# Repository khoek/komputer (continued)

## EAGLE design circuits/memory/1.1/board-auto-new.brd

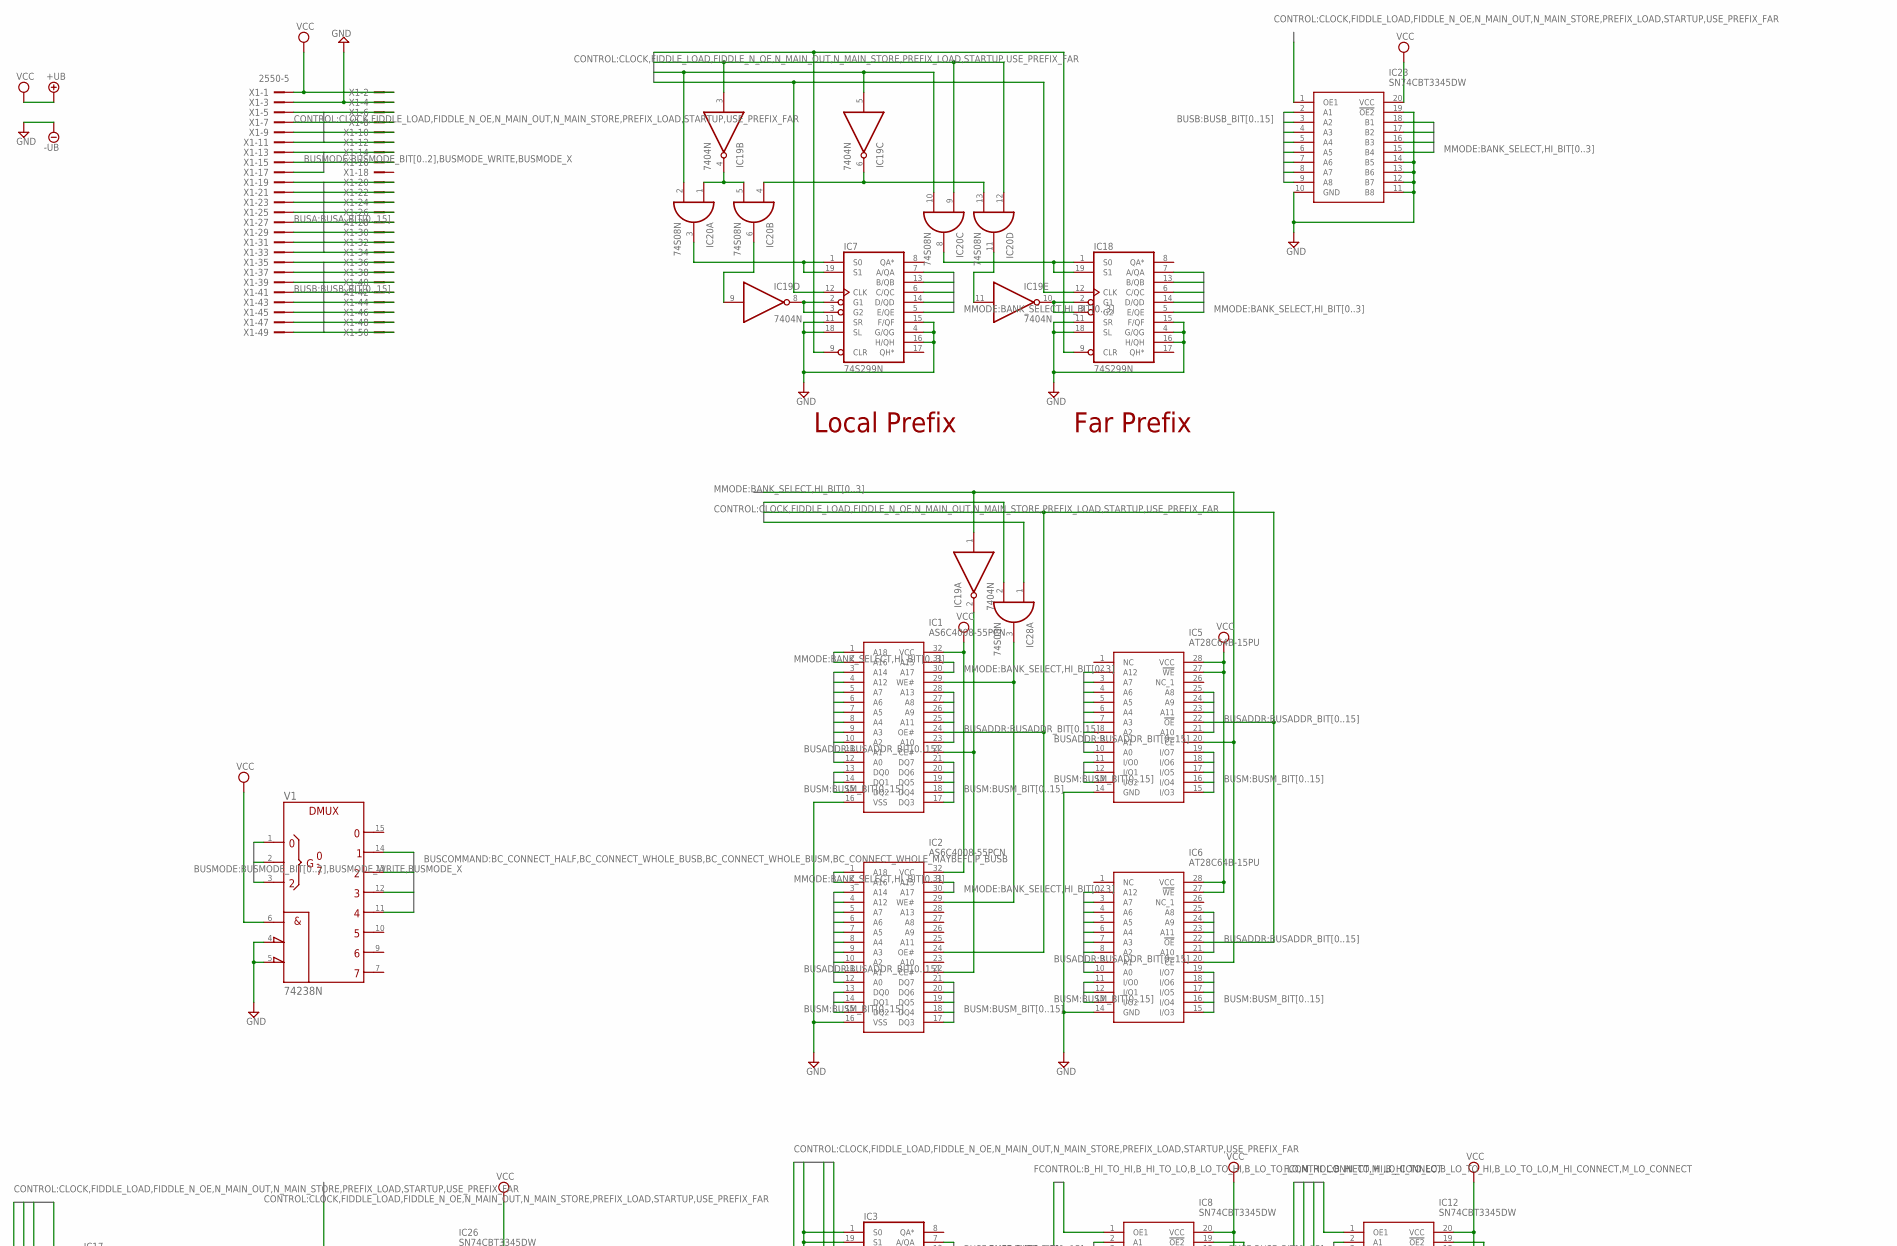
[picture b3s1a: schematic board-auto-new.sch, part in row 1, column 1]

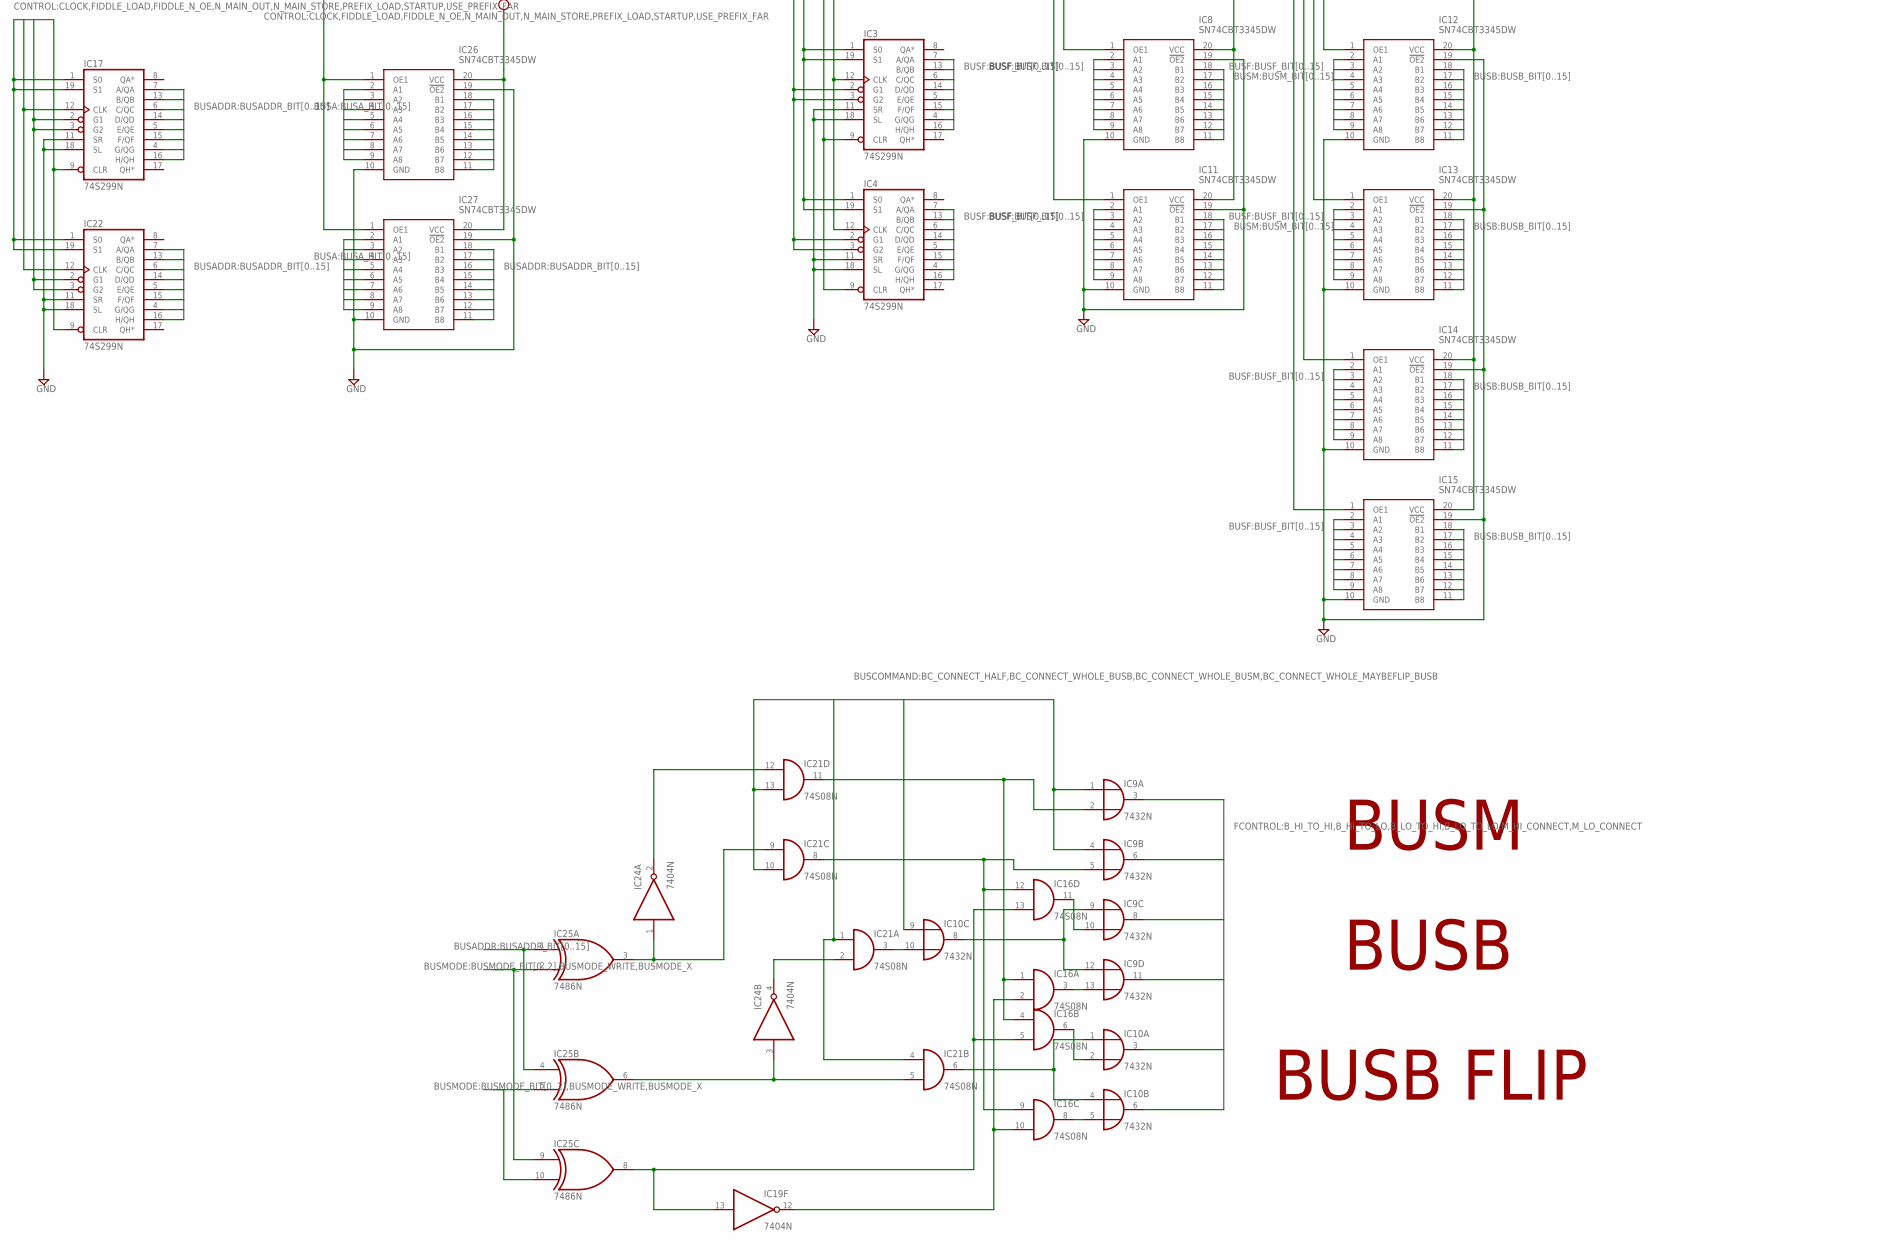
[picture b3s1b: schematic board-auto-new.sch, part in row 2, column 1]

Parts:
IC1, IC2: AS6C4008-55PCN; DIP1524W58P254L4191H406Q32N
IC3, IC4, IC7, IC17, IC18, IC22: 74S299N; DIL20
IC5, IC6: AT28C64B-15PU; DIP1556W56P254L3702H483Q28N
IC8, IC11, IC12, IC13, IC14, IC15, IC23, IC26, IC27: SN74CBT3345DW; SOIC127P1030X265-20N
IC9, IC10: 7432N; DIL14
IC16, IC20, IC21, IC28: 74S08N; DIL14
IC19, IC24: 7404N; DIL14
IC25: 7486N; DIL14
V1: 74238N; DIL16
X1: 2550-5; PAK100/2500-5-50

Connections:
BANK_SELECT: IC5.20 (!CE), IC6.20 (!CE), IC7.7 (A/QA), IC18.7 (A/QA), IC19.1 (I)
BC_CONNECT_HALF: IC21.10 (I1), IC21.13 (I1), V1.14 (Y1)
BC_CONNECT_WHOLE_BUSB: IC10.9 (I0), V1.12 (Y3)
BC_CONNECT_WHOLE_BUSM: IC9.1 (I0), IC9.4 (I0), V1.13 (Y2)
BC_CONNECT_WHOLE_MAYBEFLIP_BUSB: IC21.1 (I0), IC21.4 (I0), V1.11 (Y4)
BUSADDR_BIT0: IC17.7 (A/QA), IC25.1 (I0), IC25.4 (I0), IC26.18 (B1)
BUSADDR_BIT1: IC1.12 (A0), IC2.12 (A0), IC5.10 (A0), IC6.10 (A0), IC17.13 (B/QB), IC26.17 (B2)
BUSADDR_BIT2: IC1.11 (A1), IC2.11 (A1), IC5.9 (A1), IC6.9 (A1), IC17.6 (C/QC), IC26.16 (B3)
BUSADDR_BIT3: IC1.10 (A2), IC2.10 (A2), IC5.8 (A2), IC6.8 (A2), IC17.14 (D/QD), IC26.15 (B4)
BUSADDR_BIT4: IC1.9 (A3), IC2.9 (A3), IC5.7 (A3), IC6.7 (A3), IC17.5 (E/QE), IC26.14 (B5)
BUSADDR_BIT5: IC1.8 (A4), IC2.8 (A4), IC5.6 (A4), IC6.6 (A4), IC17.15 (F/QF), IC26.13 (B6)
BUSADDR_BIT6: IC1.7 (A5), IC2.7 (A5), IC5.5 (A5), IC6.5 (A5), IC17.4 (G/QG), IC26.12 (B7)
BUSADDR_BIT7: IC1.6 (A6), IC2.6 (A6), IC5.4 (A6), IC6.4 (A6), IC17.16 (H/QH), IC26.11 (B8)
BUSADDR_BIT8: IC1.5 (A7), IC2.5 (A7), IC5.3 (A7), IC6.3 (A7), IC22.7 (A/QA), IC27.18 (B1)
BUSADDR_BIT9: IC1.27 (A8), IC5.25 (A8), IC6.25 (A8), IC22.13 (B/QB), IC27.17 (B2)
BUSADDR_BIT10: IC1.26 (A9), IC5.24 (A9), IC6.24 (A9), IC22.6 (C/QC), IC27.16 (B3)
BUSADDR_BIT11: IC1.23 (A10), IC5.21 (A10), IC6.21 (A10), IC22.14 (D/QD), IC27.15 (B4)
BUSADDR_BIT12: IC1.25 (A11), IC5.23 (A11), IC6.23 (A11), IC22.5 (E/QE), IC27.14 (B5)
BUSADDR_BIT13: IC1.4 (A12), IC2.4 (A12), IC5.2 (A12), IC6.2 (A12), IC22.15 (F/QF), IC27.13 (B6)
BUSADDR_BIT14: IC1.28 (A13), IC22.4 (G/QG), IC27.12 (B7)
BUSADDR_BIT15: IC1.3 (A14), IC2.3 (A14), IC22.16 (H/QH), IC27.11 (B8)
BUSA_BIT0: IC26.2 (A1), X1.19
BUSA_BIT1: IC26.3 (A2), X1.20
BUSA_BIT2: IC26.4 (A3), X1.21
BUSA_BIT3: IC26.5 (A4), X1.22
BUSA_BIT4: IC26.6 (A5), X1.23
BUSA_BIT5: IC26.7 (A6), X1.24
BUSA_BIT6: IC26.8 (A7), X1.25
BUSA_BIT7: IC26.9 (A8), X1.26
BUSA_BIT8: IC27.2 (A1), X1.27
BUSA_BIT9: IC27.3 (A2), X1.28
BUSA_BIT10: IC27.4 (A3), X1.29
BUSA_BIT11: IC27.5 (A4), X1.30
BUSA_BIT12: IC27.6 (A5), X1.31
BUSA_BIT13: IC27.7 (A6), X1.32
BUSA_BIT14: IC27.8 (A7), X1.33
BUSA_BIT15: IC27.9 (A8), X1.34
BUSB_BIT0: IC12.18 (B1), IC13.18 (B1), IC23.2 (A1), X1.35
BUSB_BIT1: IC12.17 (B2), IC13.17 (B2), IC23.3 (A2), X1.36
BUSB_BIT2: IC12.16 (B3), IC13.16 (B3), IC23.4 (A3), X1.37
BUSB_BIT3: IC12.15 (B4), IC13.15 (B4), IC23.5 (A4), X1.38
BUSB_BIT4: IC12.14 (B5), IC13.14 (B5), IC23.6 (A5), X1.39
BUSB_BIT5: IC12.13 (B6), IC13.13 (B6), IC23.7 (A6), X1.40
BUSB_BIT6: IC12.12 (B7), IC13.12 (B7), IC23.8 (A7), X1.41
BUSB_BIT7: IC12.11 (B8), IC13.11 (B8), IC23.9 (A8), X1.42
BUSB_BIT8: IC14.18 (B1), IC15.18 (B1), X1.43
BUSB_BIT9: IC14.17 (B2), IC15.17 (B2), X1.44
BUSB_BIT10: IC14.16 (B3), IC15.16 (B3), X1.45
BUSB_BIT11: IC14.15 (B4), IC15.15 (B4), X1.46
BUSB_BIT12: IC14.14 (B5), IC15.14 (B5), X1.47
BUSB_BIT13: IC14.13 (B6), IC15.13 (B6), X1.48
BUSB_BIT14: IC14.12 (B7), IC15.12 (B7), X1.49
BUSB_BIT15: IC14.11 (B8), IC15.11 (B8), X1.50
BUSF_BIT0: IC3.7 (A/QA), IC8.2 (A1), IC12.2 (A1), IC14.2 (A1)
BUSF_BIT1: IC3.13 (B/QB), IC8.3 (A2), IC12.3 (A2), IC14.3 (A2)
BUSF_BIT2: IC3.6 (C/QC), IC8.4 (A3), IC12.4 (A3), IC14.4 (A3)
BUSF_BIT3: IC3.14 (D/QD), IC8.5 (A4), IC12.5 (A4), IC14.5 (A4)
BUSF_BIT4: IC3.5 (E/QE), IC8.6 (A5), IC12.6 (A5), IC14.6 (A5)
BUSF_BIT5: IC3.15 (F/QF), IC8.7 (A6), IC12.7 (A6), IC14.7 (A6)
BUSF_BIT6: IC3.4 (G/QG), IC8.8 (A7), IC12.8 (A7), IC14.8 (A7)
BUSF_BIT7: IC3.16 (H/QH), IC8.9 (A8), IC12.9 (A8), IC14.9 (A8)
BUSF_BIT8: IC4.7 (A/QA), IC11.2 (A1), IC13.2 (A1), IC15.2 (A1)
BUSF_BIT9: IC4.13 (B/QB), IC11.3 (A2), IC13.3 (A2), IC15.3 (A2)
BUSF_BIT10: IC4.6 (C/QC), IC11.4 (A3), IC13.4 (A3), IC15.4 (A3)
BUSF_BIT11: IC4.14 (D/QD), IC11.5 (A4), IC13.5 (A4), IC15.5 (A4)
BUSF_BIT12: IC4.5 (E/QE), IC11.6 (A5), IC13.6 (A5), IC15.6 (A5)
BUSF_BIT13: IC4.15 (F/QF), IC11.7 (A6), IC13.7 (A6), IC15.7 (A6)
BUSF_BIT14: IC4.4 (G/QG), IC11.8 (A7), IC13.8 (A7), IC15.8 (A7)
BUSF_BIT15: IC4.16 (H/QH), IC11.9 (A8), IC13.9 (A8), IC15.9 (A8)
BUSMODE_BIT0: V1.1 (A), X1.13
BUSMODE_BIT1: V1.2 (B), X1.15
BUSMODE_BIT2: V1.3 (C), X1.17
BUSMODE_WRITE: IC25.2 (I1), IC25.9 (I0), X1.14
BUSMODE_X: IC25.5 (I1), IC25.10 (I1), X1.16
BUSM_BIT0: IC1.13 (DQ0), IC5.11 (I/O0), IC6.11 (I/O0), IC8.18 (B1)
BUSM_BIT1: IC1.14 (DQ1), IC5.12 (I/O1), IC6.12 (I/O1), IC8.17 (B2)
BUSM_BIT2: IC1.15 (DQ2), IC5.13 (I/O2), IC6.13 (I/O2), IC8.16 (B3)
BUSM_BIT3: IC1.17 (DQ3), IC5.15 (I/O3), IC6.15 (I/O3), IC8.15 (B4)
BUSM_BIT4: IC1.18 (DQ4), IC5.16 (I/O4), IC6.16 (I/O4), IC8.14 (B5)
BUSM_BIT5: IC1.19 (DQ5), IC5.17 (I/O5), IC6.17 (I/O5), IC8.13 (B6)
BUSM_BIT6: IC1.20 (DQ6), IC5.18 (I/O6), IC6.18 (I/O6), IC8.12 (B7)
BUSM_BIT7: IC1.21 (DQ7), IC5.19 (I/O7), IC6.19 (I/O7), IC8.11 (B8)
BUSM_BIT8: IC2.13 (DQ0), IC11.18 (B1)
BUSM_BIT9: IC2.14 (DQ1), IC11.17 (B2)
BUSM_BIT10: IC2.15 (DQ2), IC11.16 (B3)
BUSM_BIT11: IC2.17 (DQ3), IC11.15 (B4)
BUSM_BIT12: IC2.18 (DQ4), IC11.14 (B5)
BUSM_BIT13: IC2.19 (DQ5), IC11.13 (B6)
BUSM_BIT14: IC2.20 (DQ6), IC11.12 (B7)
BUSM_BIT15: IC2.21 (DQ7), IC11.11 (B8)
B_HI_TO_HI: IC9.11 (O), IC15.1 (OE1)
B_HI_TO_LO: IC10.6 (O), IC14.1 (OE1)
B_LO_TO_HI: IC10.3 (O), IC13.1 (OE1)
B_LO_TO_LO: IC9.8 (O), IC12.1 (OE1)
CLOCK: IC3.12 (CLK), IC4.12 (CLK), IC7.12 (CLK), IC17.12 (CLK), IC18.12 (CLK), IC22.12 (CLK), IC28.1 (I0), X1.5
FIDDLE_LOAD: IC3.1 (S0), IC3.19 (S1), IC4.1 (S0), IC4.19 (S1), IC17.1 (S0), IC17.19 (S1), IC22.1 (S0), IC22.19 (S1), IC26.1 (OE1), IC27.1 (OE1), X1.11
FIDDLE_N_OE: IC3.2 (G1), IC3.3 (G2), IC4.2 (G1), IC4.3 (G2), IC17.2 (G1), IC17.3 (G2), IC22.2 (G1), IC22.3 (G2), X1.12
GND: IC1.16 (VSS), IC2.16 (VSS), IC3.10 (GND), IC3.11 (SR), IC3.18 (SL), IC4.10 (GND), IC4.11 (SR), IC4.18 (SL), IC5.14 (GND), IC6.14 (GND), IC7.4 (G/QG), IC7.10 (GND), IC7.11 (SR), IC7.15 (F/QF), IC7.16 (H/QH), IC7.18 (SL), IC8.10 (GND), IC8.19 (!OE2), IC9.7 (GND), IC10.7 (GND), IC11.10 (GND), IC11.19 (!OE2), IC12.10 (GND), IC12.19 (!OE2), IC13.10 (GND), IC13.19 (!OE2), IC14.10 (GND), IC14.19 (!OE2), IC15.10 (GND), IC15.19 (!OE2), IC16.7 (GND), IC17.10 (GND), IC17.11 (SR), IC17.18 (SL), IC18.4 (G/QG), IC18.10 (GND), IC18.11 (SR), IC18.15 (F/QF), IC18.16 (H/QH), IC18.18 (SL), IC19.7 (GND), IC20.7 (GND), IC21.7 (GND), IC22.10 (GND), IC22.11 (SR), IC22.18 (SL), IC23.10 (GND), IC23.11 (B8), IC23.12 (B7), IC23.13 (B6), IC23.14 (B5), IC23.19 (!OE2), IC24.7 (GND), IC25.7 (GND), IC26.10 (GND), IC26.19 (!OE2), IC27.10 (GND), IC27.19 (!OE2), IC28.7 (GND), V1.4 (!G2A), V1.5 (!G2B), V1.8 (-UB), X1.3, X1.4
HI_BIT0: IC1.31 (A15), IC2.31 (A15), IC7.13 (B/QB), IC18.13 (B/QB), IC23.18 (B1)
HI_BIT1: IC1.2 (A16), IC2.2 (A16), IC7.6 (C/QC), IC18.6 (C/QC), IC23.17 (B2)
HI_BIT2: IC1.30 (A17), IC2.30 (A17), IC7.14 (D/QD), IC18.14 (D/QD), IC23.16 (B3)
HI_BIT3: IC1.1 (A18), IC2.1 (A18), IC7.5 (E/QE), IC18.5 (E/QE), IC23.15 (B4)
M_HI_CONNECT: IC9.6 (O), IC11.1 (OE1)
M_LO_CONNECT: IC8.1 (OE1), IC9.3 (O)
unnamed: IC19.4 (O), IC20.1 (I0), IC20.5 (I1)
unnamed: IC7.1 (S0), IC7.19 (S1), IC20.3 (O)
unnamed: IC18.1 (S0), IC18.19 (S1), IC20.8 (O)
unnamed: IC18.2 (G1), IC18.3 (G2), IC19.10 (O)
unnamed: IC7.2 (G1), IC7.3 (G2), IC19.8 (O)
unnamed: IC1.22 (CE#), IC2.22 (CE#), IC19.2 (O)
unnamed: IC19.11 (I), IC20.11 (O)
unnamed: IC19.9 (I), IC20.6 (O)
unnamed: IC19.6 (O), IC20.4 (I0), IC20.13 (I1)
unnamed: IC10.1 (I0), IC10.4 (I0), IC21.6 (O)
unnamed: IC10.10 (I1), IC21.3 (O)
unnamed: IC21.2 (I1), IC24.4 (O)
unnamed: IC9.10 (I1), IC16.11 (O)
unnamed: IC21.5 (I1), IC24.3 (I), IC25.6 (O)
unnamed: IC9.5 (I1), IC16.9 (I0), IC16.12 (I0), IC21.8 (O)
unnamed: IC21.12 (I0), IC24.2 (O)
unnamed: IC21.9 (I0), IC24.1 (I), IC25.3 (O)
unnamed: IC9.9 (I0), IC9.12 (I0), IC10.8 (O)
unnamed: IC9.13 (I1), IC16.3 (O)
unnamed: IC10.2 (I1), IC16.6 (O)
unnamed: IC10.5 (I1), IC16.8 (O)
unnamed: IC9.2 (I1), IC16.1 (I0), IC16.4 (I0), IC21.11 (O)
unnamed: IC16.2 (I1), IC16.10 (I1), IC19.12 (O)
unnamed: IC16.5 (I1), IC16.13 (I1), IC19.13 (I), IC25.8 (O)
unnamed: IC1.29 (WE#), IC2.29 (WE#), IC28.3 (O)
N_MAIN_OUT: IC1.24 (OE#), IC2.24 (OE#), IC5.22 (!OE), IC6.22 (!OE), X1.9
N_MAIN_STORE: IC28.2 (I1), X1.10
PREFIX_LOAD: IC19.5 (I), IC20.2 (I1), IC20.10 (I1), IC23.1 (OE1), X1.8
STARTUP: IC3.9 (CLR), IC4.9 (CLR), IC7.9 (CLR), IC17.9 (CLR), IC18.9 (CLR), IC22.9 (CLR), X1.6
USE_PREFIX_FAR: IC19.3 (I), IC20.9 (I0), IC20.12 (I0), X1.7
VCC: IC1.32 (VCC), IC2.32 (VCC), IC3.20 (VCC), IC4.20 (VCC), IC5.27 (!WE), IC5.28 (VCC), IC6.27 (!WE), IC6.28 (VCC), IC7.20 (VCC), IC8.20 (VCC), IC9.14 (VCC), IC10.14 (VCC), IC11.20 (VCC), IC12.20 (VCC), IC13.20 (VCC), IC14.20 (VCC), IC15.20 (VCC), IC16.14 (VCC), IC17.20 (VCC), IC18.20 (VCC), IC19.14 (VCC), IC20.14 (VCC), IC21.14 (VCC), IC22.20 (VCC), IC23.20 (VCC), IC24.14 (VCC), IC25.14 (VCC), IC26.20 (VCC), IC27.20 (VCC), IC28.14 (VCC), V1.6 (G1), V1.16 (+UB), X1.1, X1.2

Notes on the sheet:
Far Prefix
Local Prefix
BUSM
BUSB
BUSB FLIP

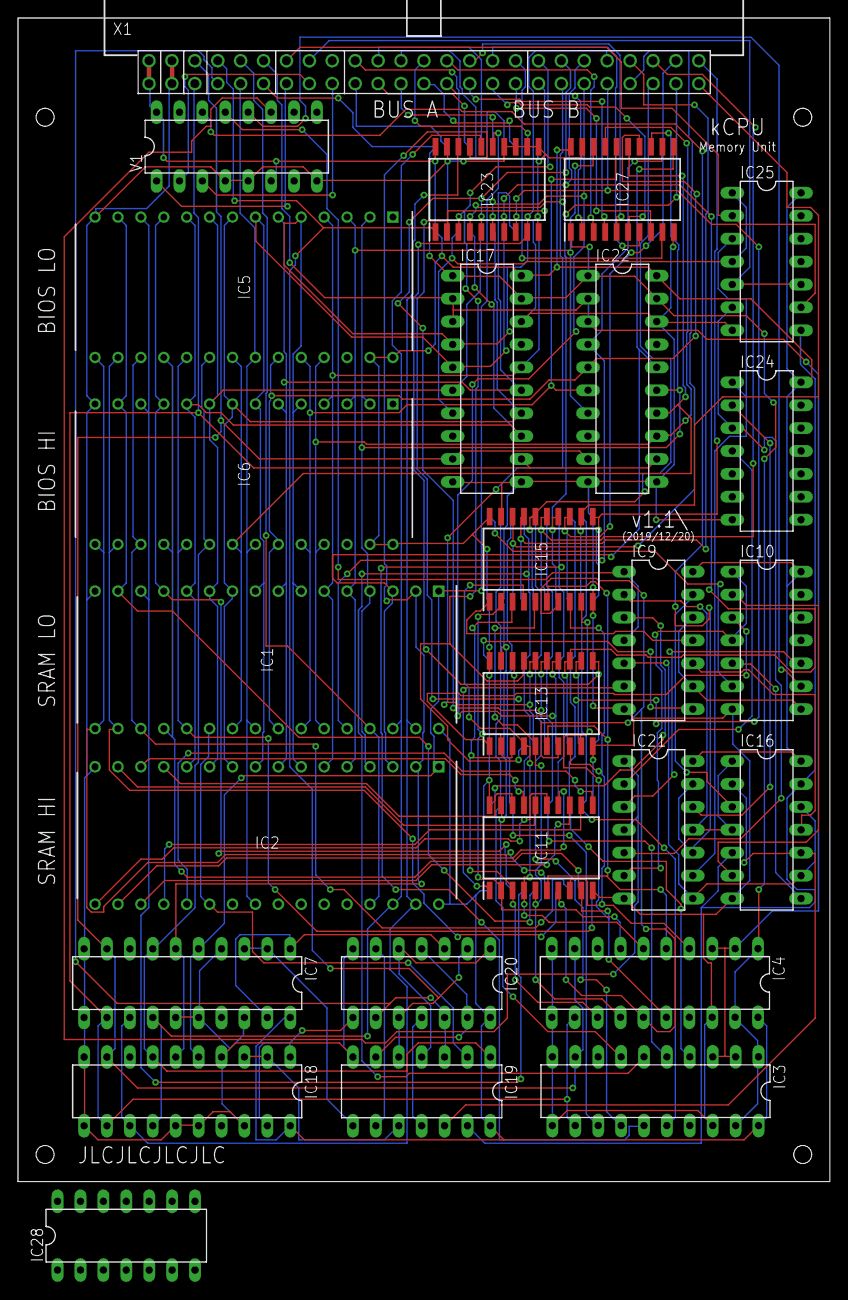
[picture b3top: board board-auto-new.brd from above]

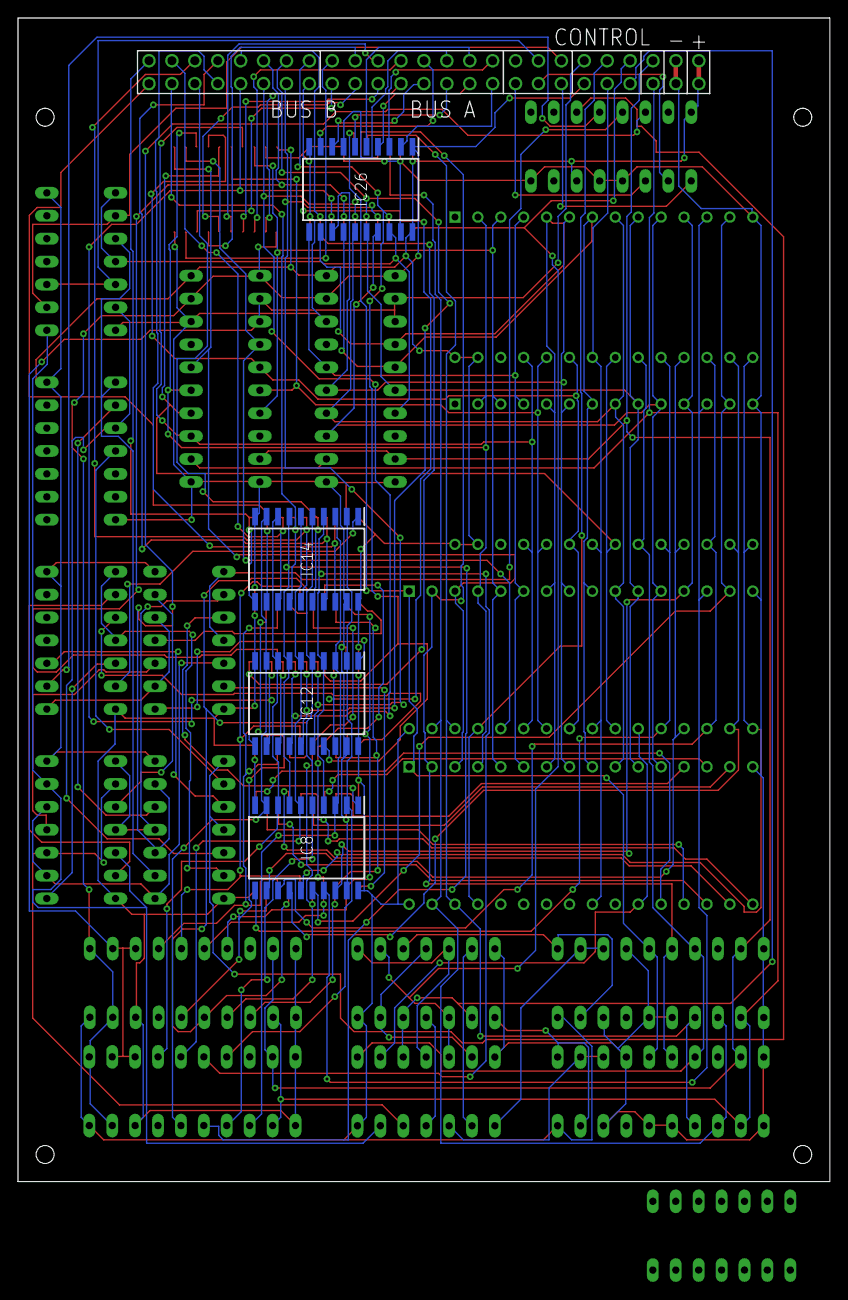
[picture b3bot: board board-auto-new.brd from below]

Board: 2 copper layers, 90.0 x 129.0 mm, 30 parts (4 on the bottom side), 135 nets.

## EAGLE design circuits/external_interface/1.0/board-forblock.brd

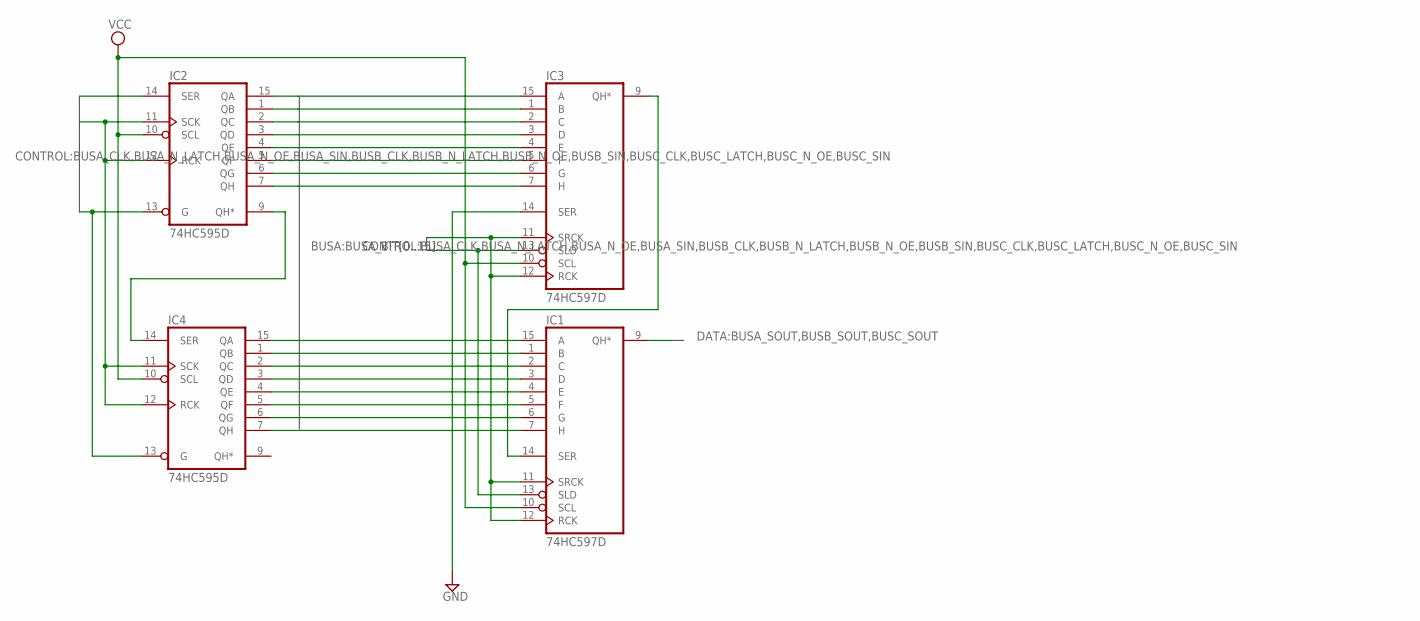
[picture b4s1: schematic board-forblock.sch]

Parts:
IC1, IC3: 74HC597D; SO16
IC2, IC4: 74HC595D; SO16

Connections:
BUSA_BIT0: IC2.15 (QA), IC3.15 (A)
BUSA_BIT1: IC2.1 (QB), IC3.1 (B)
BUSA_BIT2: IC2.2 (QC), IC3.2 (C)
BUSA_BIT3: IC2.3 (QD), IC3.3 (D)
BUSA_BIT4: IC2.4 (QE), IC3.4 (E)
BUSA_BIT5: IC2.5 (QF), IC3.5 (F)
BUSA_BIT6: IC2.6 (QG), IC3.6 (G)
BUSA_BIT7: IC2.7 (QH), IC3.7 (H)
BUSA_BIT8: IC1.15 (A), IC4.15 (QA)
BUSA_BIT9: IC1.1 (B), IC4.1 (QB)
BUSA_BIT10: IC1.2 (C), IC4.2 (QC)
BUSA_BIT11: IC1.3 (D), IC4.3 (QD)
BUSA_BIT12: IC1.4 (E), IC4.4 (QE)
BUSA_BIT13: IC1.5 (F), IC4.5 (QF)
BUSA_BIT14: IC1.6 (G), IC4.6 (QG)
BUSA_BIT15: IC1.7 (H), IC4.7 (QH)
BUSA_CLK: IC1.11 (SRCK), IC1.12 (RCK), IC2.11 (SCK), IC2.12 (RCK), IC3.11 (SRCK), IC3.12 (RCK), IC4.11 (SCK), IC4.12 (RCK)
BUSA_N_LATCH: IC1.13 (SLD), IC3.13 (SLD)
BUSA_N_OE: IC2.13 (G), IC4.13 (G)
BUSA_SIN: IC2.14 (SER)
BUSA_SOUT: IC1.9 (QH*)
GND: IC1.8 (GND), IC2.8 (GND), IC3.8 (GND), IC3.14 (SER), IC4.8 (GND)
unnamed: IC2.9 (QH*), IC4.14 (SER)
unnamed: IC1.14 (SER), IC3.9 (QH*)
VCC: IC1.10 (SCL), IC1.16 (VCC), IC2.10 (SCL), IC2.16 (VCC), IC3.10 (SCL), IC3.16 (VCC), IC4.10 (SCL), IC4.16 (VCC)

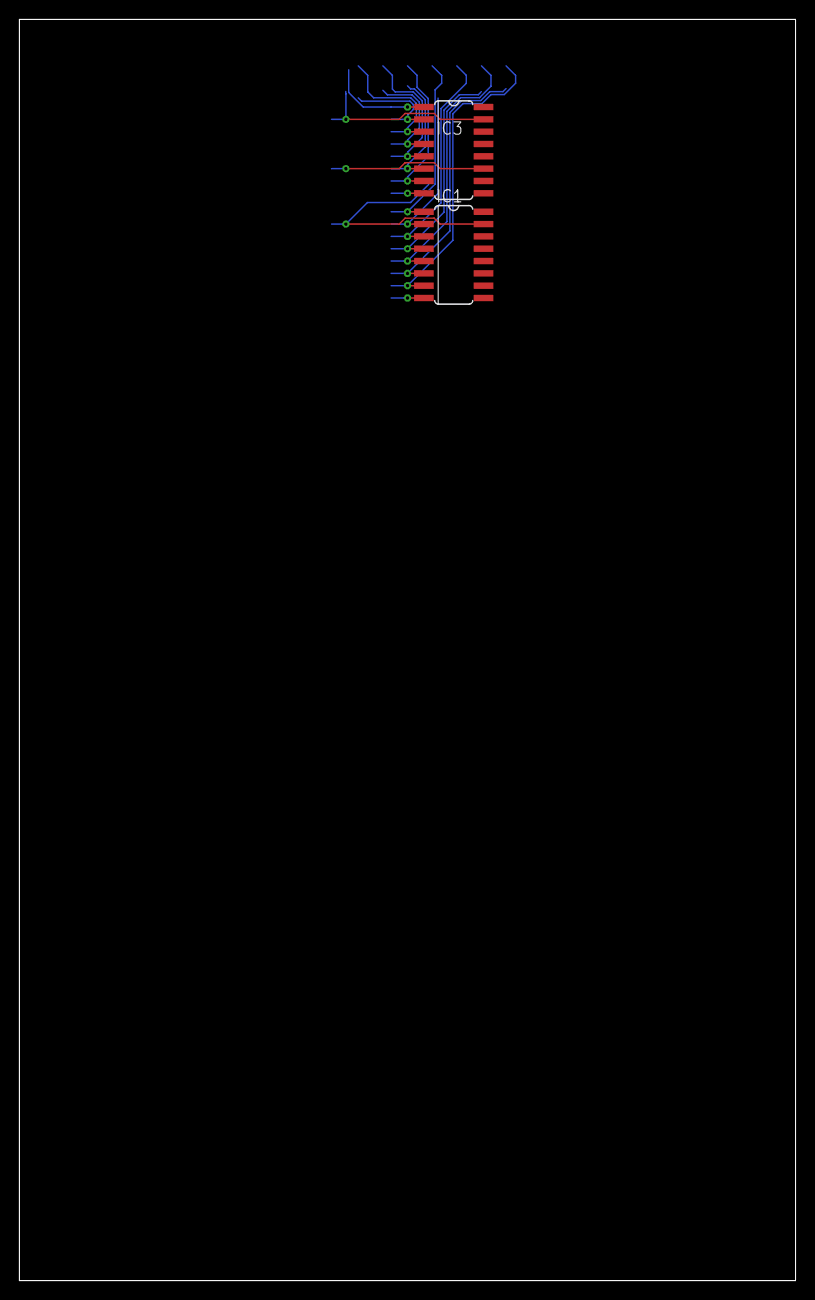
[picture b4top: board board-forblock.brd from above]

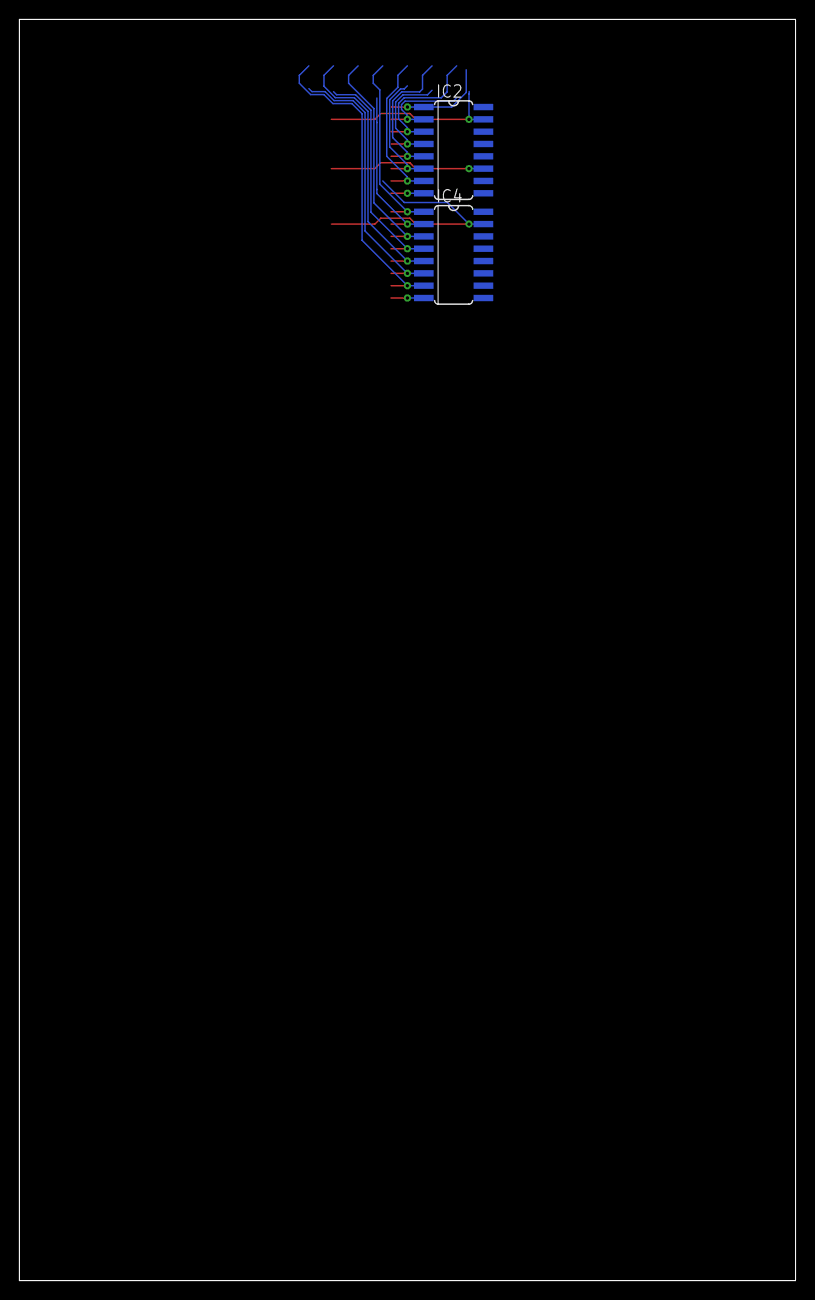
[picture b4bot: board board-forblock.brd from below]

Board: 2 copper layers, 80.0 x 130.0 mm, 4 parts (2 on the bottom side), 23 nets.

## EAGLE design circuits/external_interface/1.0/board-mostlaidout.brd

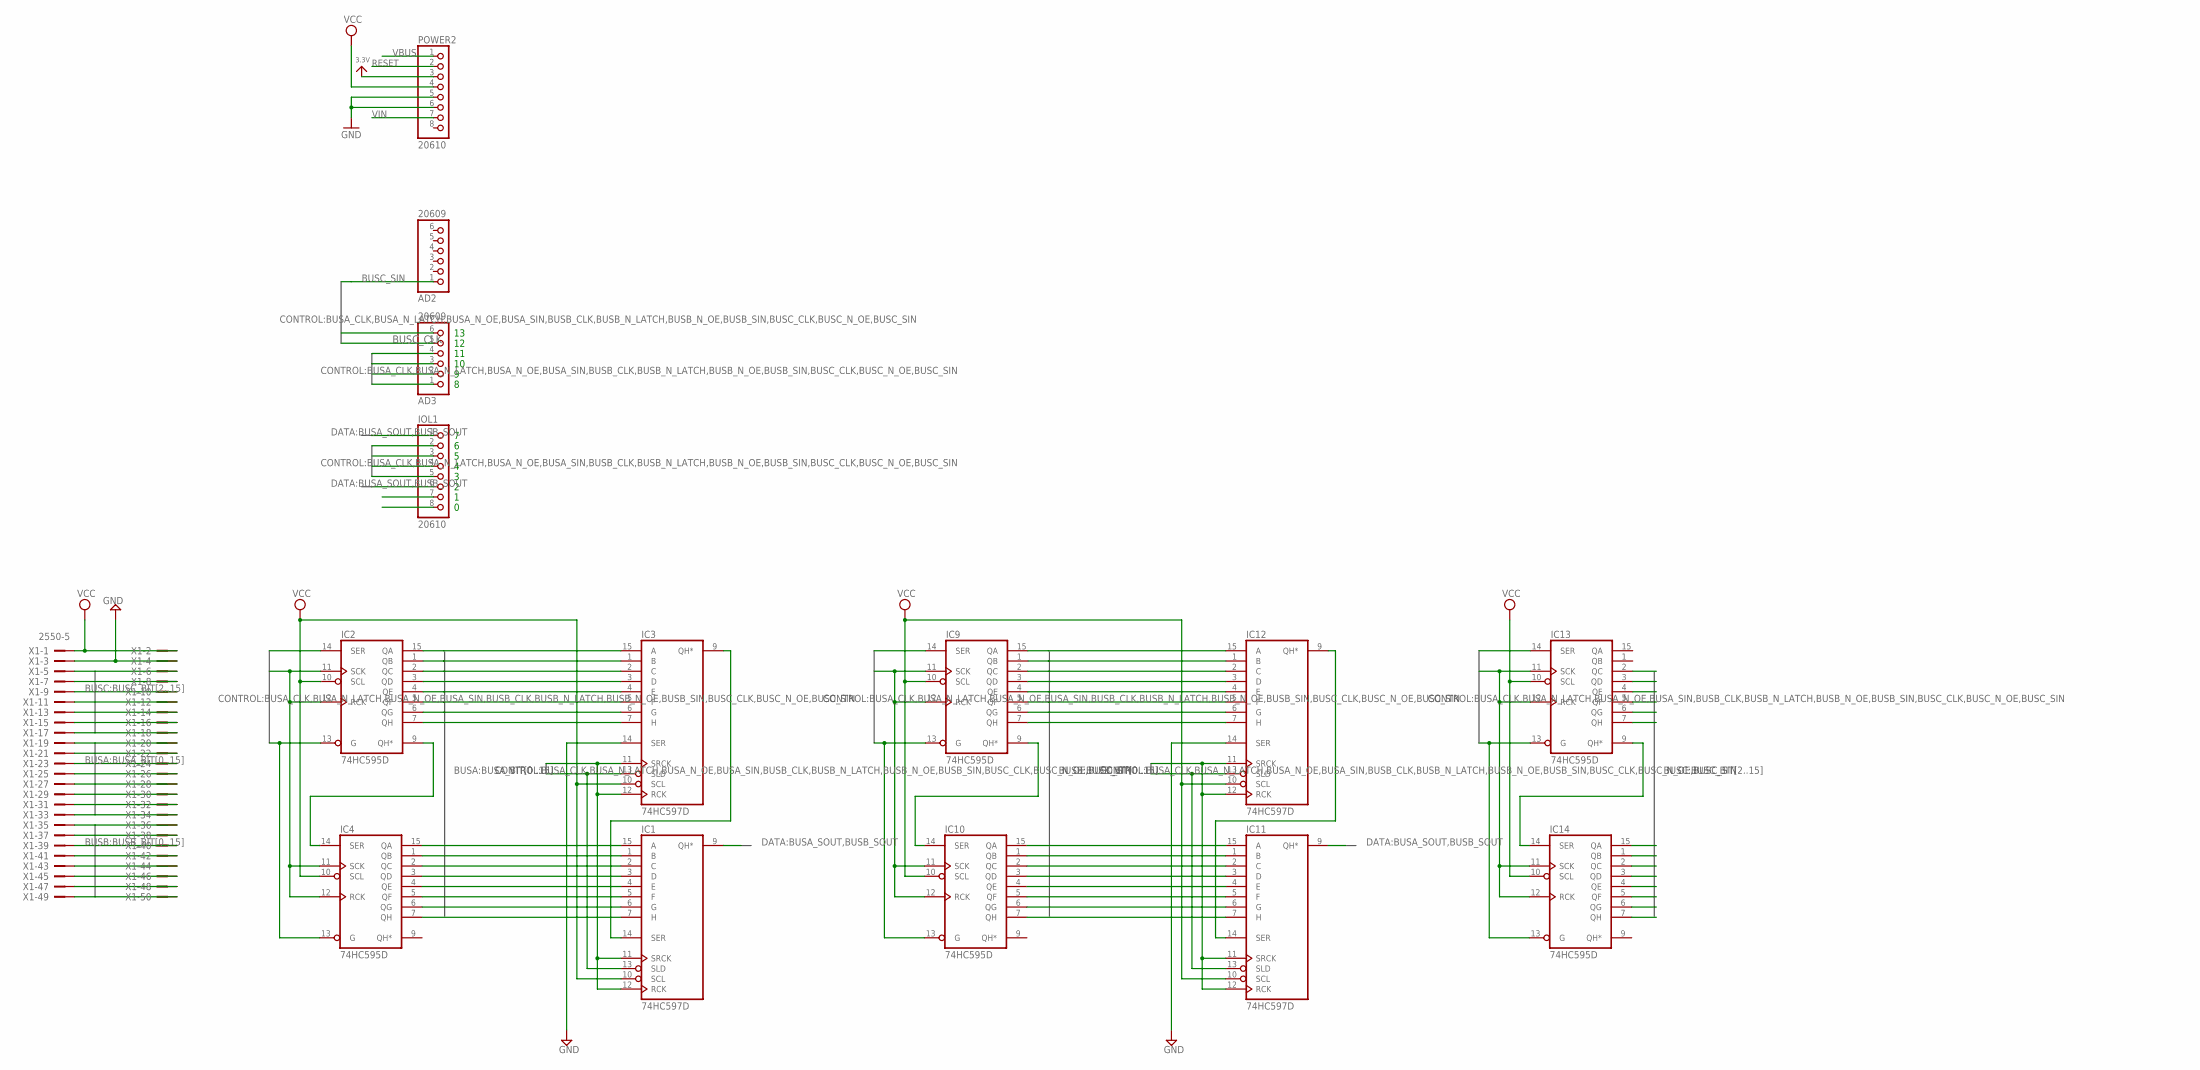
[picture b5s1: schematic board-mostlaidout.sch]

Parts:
AD2, AD3: 20609; 1X06_ROUND
IC1, IC3, IC11, IC12: 74HC597D; SO16
IC2, IC4, IC9, IC10, IC13, IC14: 74HC595D; SO16
IOL1: 20610; 1X08_ROUND
POWER2: 20610; 1X08_ROUND_70
X1: 2550-5; PAK100/2500-5-50

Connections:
3.3V: POWER2.3
BUSA_BIT0: IC2.15 (QA), IC3.15 (A), X1.19
BUSA_BIT1: IC2.1 (QB), IC3.1 (B), X1.20
BUSA_BIT2: IC2.2 (QC), IC3.2 (C), X1.21
BUSA_BIT3: IC2.3 (QD), IC3.3 (D), X1.22
BUSA_BIT4: IC2.4 (QE), IC3.4 (E), X1.23
BUSA_BIT5: IC2.5 (QF), IC3.5 (F), X1.24
BUSA_BIT6: IC2.6 (QG), IC3.6 (G), X1.25
BUSA_BIT7: IC2.7 (QH), IC3.7 (H), X1.26
BUSA_BIT8: IC1.15 (A), IC4.15 (QA), X1.27
BUSA_BIT9: IC1.1 (B), IC4.1 (QB), X1.28
BUSA_BIT10: IC1.2 (C), IC4.2 (QC), X1.29
BUSA_BIT11: IC1.3 (D), IC4.3 (QD), X1.30
BUSA_BIT12: IC1.4 (E), IC4.4 (QE), X1.31
BUSA_BIT13: IC1.5 (F), IC4.5 (QF), X1.32
BUSA_BIT14: IC1.6 (G), IC4.6 (QG), X1.33
BUSA_BIT15: IC1.7 (H), IC4.7 (QH), X1.34
BUSA_CLK: AD3.1, IC1.11 (SRCK), IC1.12 (RCK), IC2.11 (SCK), IC2.12 (RCK), IC3.11 (SRCK), IC3.12 (RCK), IC4.11 (SCK), IC4.12 (RCK)
BUSA_N_LATCH: AD3.2, IC1.13 (SLD), IC3.13 (SLD)
BUSA_N_OE: AD3.3, IC2.13 (G), IC4.13 (G)
BUSA_SIN: AD3.4, IC2.14 (SER)
BUSA_SOUT: IC1.9 (QH*), IOL1.1
BUSB_BIT0: IC9.15 (QA), IC12.15 (A), X1.35
BUSB_BIT1: IC9.1 (QB), IC12.1 (B), X1.36
BUSB_BIT2: IC9.2 (QC), IC12.2 (C), X1.37
BUSB_BIT3: IC9.3 (QD), IC12.3 (D), X1.38
BUSB_BIT4: IC9.4 (QE), IC12.4 (E), X1.39
BUSB_BIT5: IC9.5 (QF), IC12.5 (F), X1.40
BUSB_BIT6: IC9.6 (QG), IC12.6 (G), X1.41
BUSB_BIT7: IC9.7 (QH), IC12.7 (H), X1.42
BUSB_BIT8: IC10.15 (QA), IC11.15 (A), X1.43
BUSB_BIT9: IC10.1 (QB), IC11.1 (B), X1.44
BUSB_BIT10: IC10.2 (QC), IC11.2 (C), X1.45
BUSB_BIT11: IC10.3 (QD), IC11.3 (D), X1.46
BUSB_BIT12: IC10.4 (QE), IC11.4 (E), X1.47
BUSB_BIT13: IC10.5 (QF), IC11.5 (F), X1.48
BUSB_BIT14: IC10.6 (QG), IC11.6 (G), X1.49
BUSB_BIT15: IC10.7 (QH), IC11.7 (H), X1.50
BUSB_CLK: IC9.11 (SCK), IC9.12 (RCK), IC10.11 (SCK), IC10.12 (RCK), IC11.11 (SRCK), IC11.12 (RCK), IC12.11 (SRCK), IC12.12 (RCK), IOL1.5
BUSB_N_LATCH: IC11.13 (SLD), IC12.13 (SLD), IOL1.4
BUSB_N_OE: IC9.13 (G), IC10.13 (G), IOL1.3
BUSB_SIN: IC9.14 (SER), IOL1.2
BUSB_SOUT: IC11.9 (QH*), IOL1.6
BUSC_BIT2: IC13.2 (QC), X1.5
BUSC_BIT3: IC13.3 (QD), X1.6
BUSC_BIT4: IC13.4 (QE), X1.7
BUSC_BIT5: IC13.5 (QF), X1.8
BUSC_BIT6: IC13.6 (QG), X1.9
BUSC_BIT7: IC13.7 (QH), X1.10
BUSC_BIT8: IC14.15 (QA), X1.11
BUSC_BIT9: IC14.1 (QB), X1.12
BUSC_BIT10: IC14.2 (QC), X1.13
BUSC_BIT11: IC14.3 (QD), X1.14
BUSC_BIT12: IC14.4 (QE), X1.15
BUSC_BIT13: IC14.5 (QF), X1.16
BUSC_BIT14: IC14.6 (QG), X1.17
BUSC_BIT15: IC14.7 (QH), X1.18
BUSC_CLK: AD3.5, IC13.11 (SCK), IC13.12 (RCK), IC14.11 (SCK), IC14.12 (RCK)
BUSC_N_OE: AD3.6, IC13.13 (G), IC14.13 (G)
BUSC_SIN: AD2.1, IC13.14 (SER)
GND: IC1.8 (GND), IC2.8 (GND), IC3.8 (GND), IC3.14 (SER), IC4.8 (GND), IC9.8 (GND), IC10.8 (GND), IC11.8 (GND), IC12.8 (GND), IC12.14 (SER), IC13.8 (GND), IC14.8 (GND), POWER2.5, POWER2.6, X1.3, X1.4
unnamed: IC2.9 (QH*), IC4.14 (SER)
unnamed: IC1.14 (SER), IC3.9 (QH*)
unnamed: IC9.9 (QH*), IC10.14 (SER)
unnamed: IC11.14 (SER), IC12.9 (QH*)
unnamed: IC13.9 (QH*), IC14.14 (SER)
RESET: POWER2.2
RXD1: IOL1.8
TXD1: IOL1.7
VBUS: POWER2.1
VCC: IC1.10 (SCL), IC1.16 (VCC), IC2.10 (SCL), IC2.16 (VCC), IC3.10 (SCL), IC3.16 (VCC), IC4.10 (SCL), IC4.16 (VCC), IC9.10 (SCL), IC9.16 (VCC), IC10.10 (SCL), IC10.16 (VCC), IC11.10 (SCL), IC11.16 (VCC), IC12.10 (SCL), IC12.16 (VCC), IC13.10 (SCL), IC13.16 (VCC), IC14.10 (SCL), IC14.16 (VCC), POWER2.4, X1.1, X1.2
VIN: POWER2.7
